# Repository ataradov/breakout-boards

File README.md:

## Breakout Boards

This is a collection of random breakout boards I developed to get started with a new device.

Firmware for the SAM D11 used as a debugger/VCP interface on some boards is available [here](https://github.com/ataradov/free-dap))

### Currrently available boards:

* Atmel SAME70 / SAMS70
* ST STM32G071
* GigaDevice GD32F407V (will probably work for STM32F407 as well)
* Lattice LCMXO256C
* Lattice LCMXO2-2000HC
* Nuvoton M484SIDAE
* Atmel SAMD11 USB Test Board
* Atmel SAMD11 Nano - full breakout with USB connector
* Raspberry Pi RP2040
* Gowin GW1N-UV9QN48

### Errata

The boards are added here at the same time they are submitted for fabrication. There may be issues with them,
but I will not know about them until the boards arrive. Those issues will not be fixed in the files, unless
the boards are really broken and I need to reorder them, or I want to reorder them for some other reason.

Below is a list of known issues:
1. GD32F407V - BOOT0 (pin 94) should be pulled down by a 10 kOhm resistor. This is an easy fix, there is a groud pour near the jumper.
2. SAMD11 USB Test Board - Switch footprint is slightly off (mounting pads are wider than on a real switch).

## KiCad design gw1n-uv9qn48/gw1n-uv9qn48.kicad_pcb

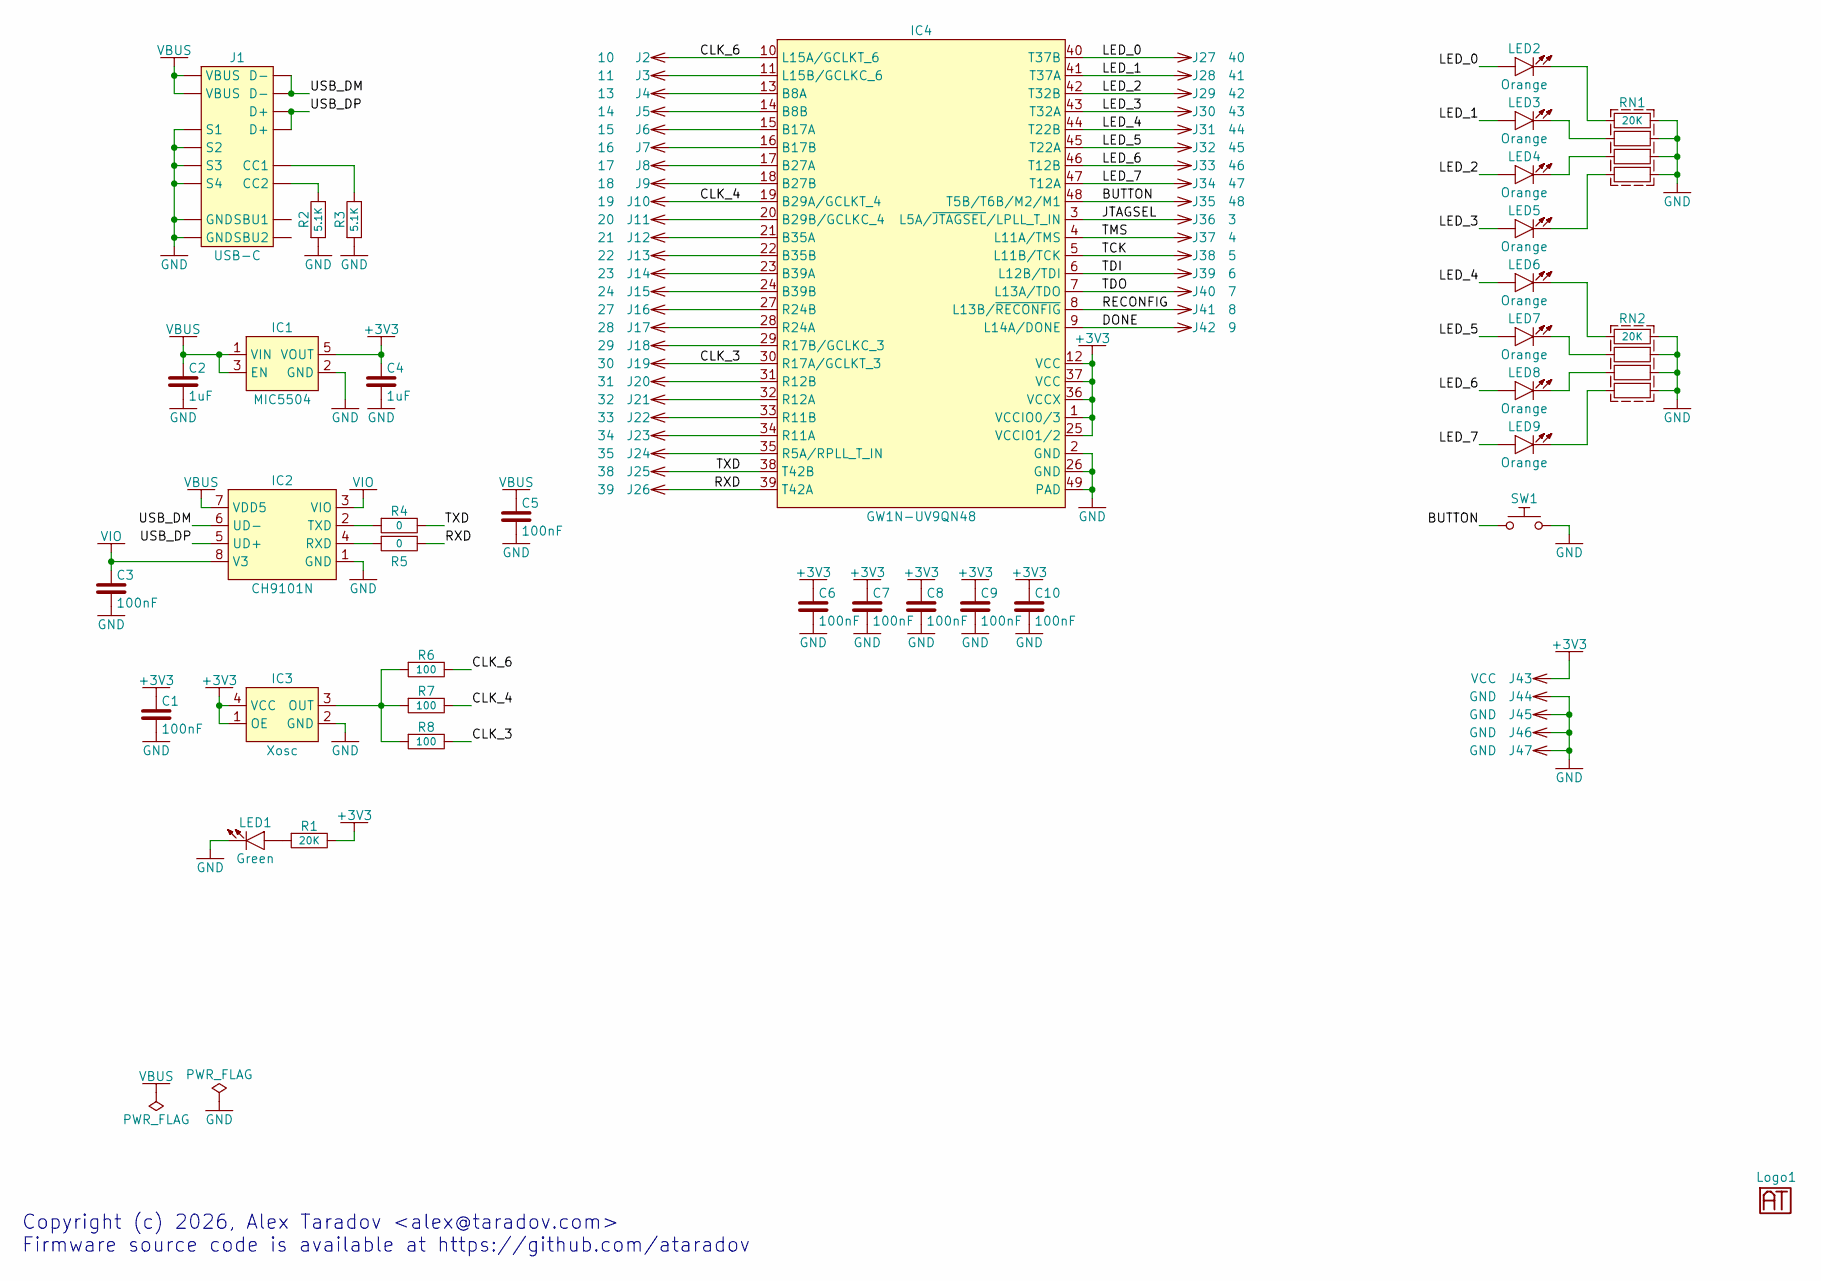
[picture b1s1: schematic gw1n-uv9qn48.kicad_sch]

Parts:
C1, C3, C5, C6, C7, C8, C9, C10: 100nF; 0603
C2, C4: 1uF; 0603
IC1: MIC5504; SOT-23-5
IC2: CH9101N; SO-8
IC3: Xosc; CDFN-4-3.2x2.5mm
IC4: GW1N-UV9QN48; QFN-48-0.4mm
J1: USB-C
J2: 10; Pin-2.54mm
J3: 11; Pin-2.54mm
J4: 13; Pin-2.54mm
J5: 14; Pin-2.54mm
J6: 15; Pin-2.54mm
J7: 16; Pin-2.54mm
J8: 17; Pin-2.54mm
J9: 18; Pin-2.54mm
J10: 19; Pin-2.54mm
J11: 20; Pin-2.54mm
J12: 21; Pin-2.54mm
J13: 22; Pin-2.54mm
J14: 23; Pin-2.54mm
J15: 24; Pin-2.54mm
J16: 27; Pin-2.54mm
J17: 28; Pin-2.54mm
J18: 29; Pin-2.54mm
J19: 30; Pin-2.54mm
J20: 31; Pin-2.54mm
J21: 32; Pin-2.54mm
J22: 33; Pin-2.54mm
J23: 34; Pin-2.54mm
J24: 35; Pin-2.54mm
J25: 38; Pin-2.54mm
J26: 39; Pin-2.54mm
J27: 40; Pin-2.54mm
J28: 41; Pin-2.54mm
J29: 42; Pin-2.54mm
J30: 43; Pin-2.54mm
J31: 44; Pin-2.54mm
J32: 45; Pin-2.54mm
J33: 46; Pin-2.54mm
J34: 47; Pin-2.54mm
J35: 48; Pin-2.54mm
J36: 3; Pin-2.54mm
J37: 4; Pin-2.54mm
J38: 5; Pin-2.54mm
J39: 6; Pin-2.54mm
J40: 7; Pin-2.54mm
J41: 8; Pin-2.54mm
J42: 9; Pin-2.54mm
J43: VCC; Pin-2.54mm
J44, J45, J46, J47: GND; Pin-2.54mm
LED1: Green; 0603_LED
LED2, LED3, LED4, LED5, LED6, LED7, LED8, LED9: Orange; 0603_LED
Logo1: Logo; Logo-Small
R1: 20K; 0603
R2, R3: 5.1K; 0603
R4, R5: 0; 0603
R6, R7, R8: 100; 0603
RN1, RN2: 20K; 0603x4
SW1: TactSwitch; TactSwitch-6mm-Sqare-SMD

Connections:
+3V3: C1.2, C4.2, C6.2, C7.2, C8.2, C9.2, C10.2, IC1.5 (VOUT), IC3.1 (OE), IC3.4 (VCC), IC4.1 (VCCIO0/3), IC4.12 (VCC), IC4.25 (VCCIO1/2), IC4.36 (VCCX), IC4.37 (VCC), J43.1 (1_1), R1.2
/BUTTON: IC4.48 (T5B/T6B/M2/M1), J35.1 (1_1), SW1.1
/CLK_3: IC4.30 (R17A/GCLKT_3), J19.1 (1_1), R8.2
/CLK_4: IC4.19 (B29A/GCLKT_4), J10.1 (1_1), R7.2
/CLK_6: IC4.10 (L15A/GCLKT_6), J2.1 (1_1), R6.2
/DONE: IC4.9 (L14A/DONE), J42.1 (1_1)
/JTAGSEL: IC4.3 (L5A/~JTAGSEL/LPLL_T_IN), J36.1 (1_1)
/LED_0: IC4.40 (T37B), J27.1 (1_1), LED2.1 (A)
/LED_1: IC4.41 (T37A), J28.1 (1_1), LED3.1 (A)
/LED_2: IC4.42 (T32B), J29.1 (1_1), LED4.1 (A)
/LED_3: IC4.43 (T32A), J30.1 (1_1), LED5.1 (A)
/LED_4: IC4.44 (T22B), J31.1 (1_1), LED6.1 (A)
/LED_5: IC4.45 (T22A), J32.1 (1_1), LED7.1 (A)
/LED_6: IC4.46 (T12B), J33.1 (1_1), LED8.1 (A)
/LED_7: IC4.47 (T12A), J34.1 (1_1), LED9.1 (A)
/RECONFIG: IC4.8 (L13B/~RECONFIG), J41.1 (1_1)
/RXD: IC4.39 (T42A), J26.1 (1_1), R5.2
/TCK: IC4.5 (L11B/TCK), J38.1 (1_1)
/TDI: IC4.6 (L12B/TDI), J39.1 (1_1)
/TDO: IC4.7 (L13A/TDO), J40.1 (1_1)
/TMS: IC4.4 (L11A/TMS), J37.1 (1_1)
/TXD: IC4.38 (T42B), J25.1 (1_1), R4.2
/USB_DM: IC2.6 (UD-), J1.D-1 (D-), J1.D-2 (D-)
/USB_DP: IC2.5 (UD+), J1.D+1 (D+), J1.D+2 (D+)
GND: C1.1, C2.1, C3.1, C4.1, C5.1, C6.1, C7.1, C8.1, C9.1, C10.1, IC1.2 (GND), IC2.1 (GND), IC3.2 (GND), IC4.2 (GND), IC4.26 (GND), IC4.49 (PAD), J1.GND1 (GND), J1.GND2 (GND), J1.S1, J1.S2, J1.S3, J1.S4, J44.1 (1_1), J45.1 (1_1), J46.1 (1_1), J47.1 (1_1), LED1.2 (K), R2.1, R3.1, RN1.1, RN1.2, RN1.3, RN1.4, RN2.1, RN2.2, RN2.3, RN2.4, SW1.2
unnamed: IC2.4 (RXD), R5.1
unnamed: IC2.2 (TXD), R4.1
unnamed: IC3.3 (OUT), R6.1, R7.1, R8.1
unnamed: IC4.13 (B8A), J4.1 (1_1)
unnamed: IC4.14 (B8B), J5.1 (1_1)
unnamed: IC4.15 (B17A), J6.1 (1_1)
unnamed: IC4.16 (B17B), J7.1 (1_1)
unnamed: IC4.17 (B27A), J8.1 (1_1)
unnamed: IC4.18 (B27B), J9.1 (1_1)
unnamed: IC4.20 (B29B/GCLKC_4), J11.1 (1_1)
unnamed: IC4.21 (B35A), J12.1 (1_1)
unnamed: IC4.22 (B35B), J13.1 (1_1)
unnamed: IC4.23 (B39A), J14.1 (1_1)
unnamed: IC4.24 (B39B), J15.1 (1_1)
unnamed: IC4.11 (L15B/GCLKC_6), J3.1 (1_1)
unnamed: IC4.35 (R5A/RPLL_T_IN), J24.1 (1_1)
unnamed: IC4.34 (R11A), J23.1 (1_1)
unnamed: IC4.33 (R11B), J22.1 (1_1)
unnamed: IC4.32 (R12A), J21.1 (1_1)
unnamed: IC4.31 (R12B), J20.1 (1_1)
unnamed: IC4.29 (R17B/GCLKC_3), J18.1 (1_1)
unnamed: IC4.28 (R24A), J17.1 (1_1)
unnamed: IC4.27 (R24B), J16.1 (1_1)
unnamed: J1.CC1, R3.2
unnamed: J1.CC2, R2.2
unnamed: LED1.1 (A), R1.1
unnamed: LED2.2 (K), RN1.8
unnamed: LED3.2 (K), RN1.7
unnamed: LED4.2 (K), RN1.6
unnamed: LED5.2 (K), RN1.5
unnamed: LED6.2 (K), RN2.8
unnamed: LED7.2 (K), RN2.7
unnamed: LED8.2 (K), RN2.6
unnamed: LED9.2 (K), RN2.5
VBUS: C2.2, C5.2, IC1.1 (VIN), IC1.3 (EN), IC2.7 (VDD5), J1.VBUS1 (VBUS), J1.VBUS2 (VBUS)
VIO: C3.2, IC2.3 (VIO), IC2.8 (V3)

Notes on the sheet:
Copyright (c) 2026, Alex Taradov <alex@taradov.com> Firmware source code is available at https://github.com/ataradov

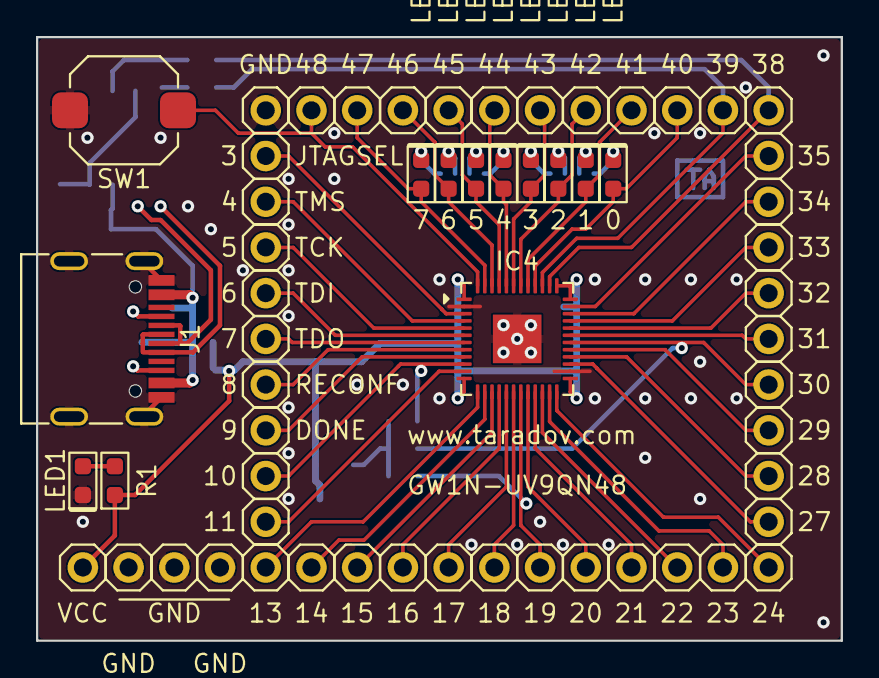
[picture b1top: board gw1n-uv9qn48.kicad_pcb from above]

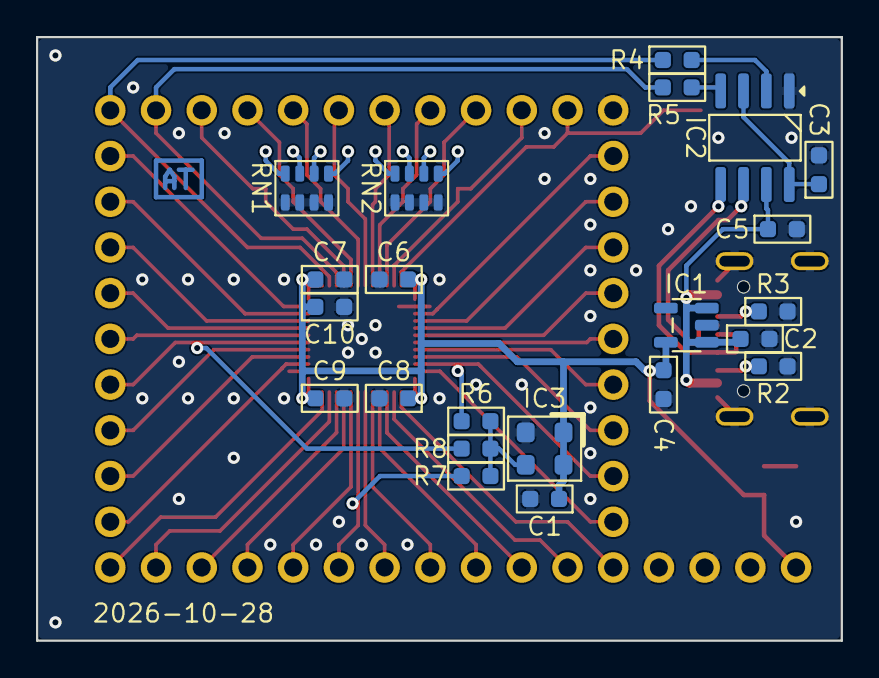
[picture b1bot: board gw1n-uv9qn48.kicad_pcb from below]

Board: 2 copper layers, 44.7 x 33.5 mm, 82 parts (23 on the bottom side), 61 nets.

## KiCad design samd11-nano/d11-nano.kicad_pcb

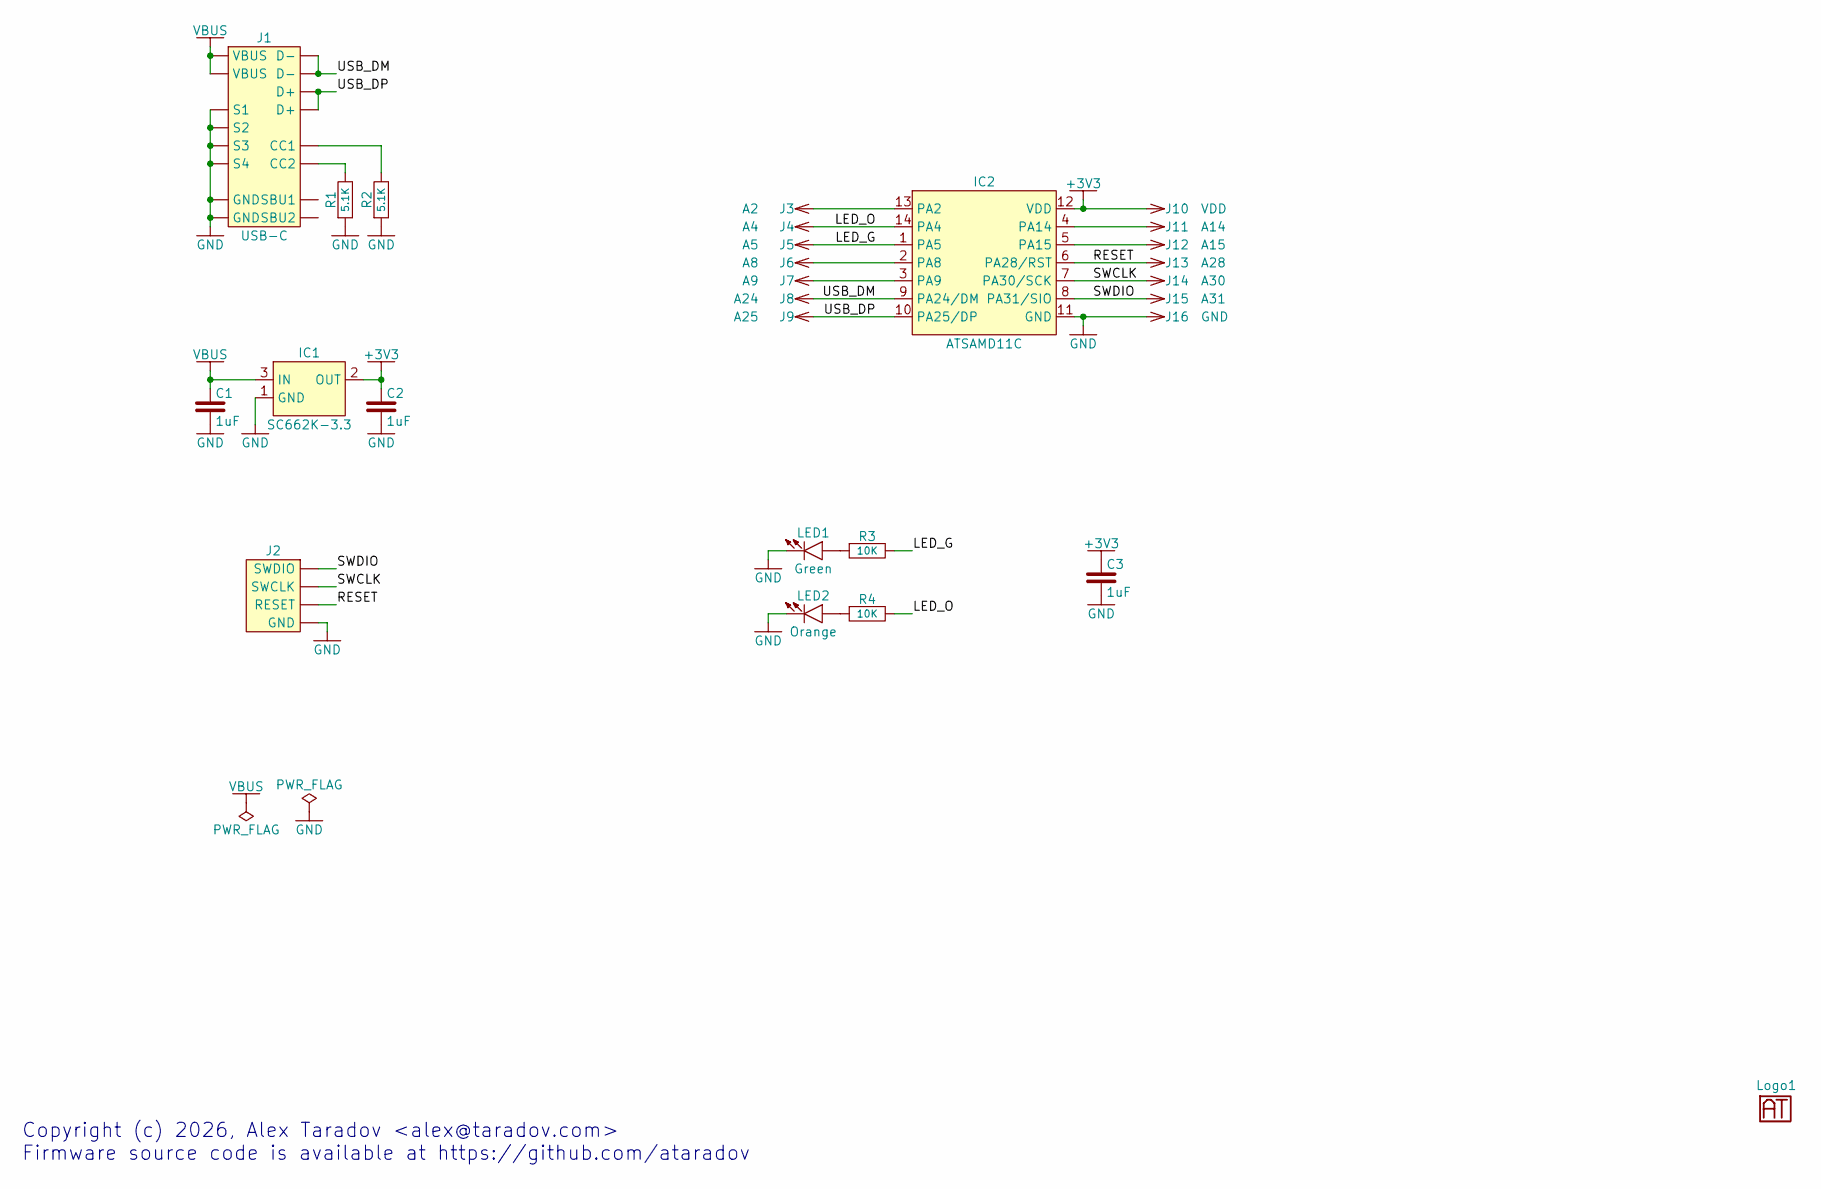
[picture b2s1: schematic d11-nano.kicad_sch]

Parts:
C1, C2, C3: 1uF; 0603
IC1: SC662K-3.3; SOT-23
IC2: ATSAMD11C; SOIC-14
J1: USB-C
J2: Debug; Debug-GDCR-2.54mm-SMD
J3: A2; Pin-2.54mm
J4: A4; Pin-2.54mm
J5: A5; Pin-2.54mm
J6: A8; Pin-2.54mm
J7: A9; Pin-2.54mm
J8: A24; Pin-2.54mm
J9: A25; Pin-2.54mm
J10: VDD; Pin-2.54mm
J11: A14; Pin-2.54mm
J12: A15; Pin-2.54mm
J13: A28; Pin-2.54mm
J14: A30; Pin-2.54mm
J15: A31; Pin-2.54mm
J16: GND; Pin-2.54mm
LED1: Green; 0603_LED
LED2: Orange; 0603_LED
Logo1: Logo; Logo-Small
R1, R2: 5.1K; 0603
R3, R4: 10K; 0603

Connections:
+3V3: C2.2, C3.2, IC1.2 (OUT), IC2.12 (VDD), J10.1 (1_1)
/LED_G: IC2.1 (PA5), J5.1 (1_1), R3.2
/LED_O: IC2.14 (PA4), J4.1 (1_1), R4.2
/RESET: IC2.6 (PA28/RST), J2.RESET, J13.1 (1_1)
/SWCLK: IC2.7 (PA30/SCK), J2.SWCLK, J14.1 (1_1)
/SWDIO: IC2.8 (PA31/SIO), J2.SWDIO, J15.1 (1_1)
/USB_DM: IC2.9 (PA24/DM), J1.D-1 (D-), J1.D-2 (D-), J8.1 (1_1)
/USB_DP: IC2.10 (PA25/DP), J1.D+1 (D+), J1.D+2 (D+), J9.1 (1_1)
GND: C1.1, C2.1, C3.1, IC1.1 (GND), IC2.11 (GND), J1.GND1 (GND), J1.GND2 (GND), J1.S1, J1.S2, J1.S3, J1.S4, J2.GND, J16.1 (1_1), LED1.2 (K), LED2.2 (K), R1.1, R2.1
unnamed: IC2.13 (PA2), J3.1 (1_1)
unnamed: IC2.2 (PA8), J6.1 (1_1)
unnamed: IC2.3 (PA9), J7.1 (1_1)
unnamed: IC2.4 (PA14), J11.1 (1_1)
unnamed: IC2.5 (PA15), J12.1 (1_1)
unnamed: J1.CC1, R2.2
unnamed: J1.CC2, R1.2
unnamed: LED1.1 (A), R3.1
unnamed: LED2.1 (A), R4.1
VBUS: C1.2, IC1.3 (IN), J1.VBUS1 (VBUS), J1.VBUS2 (VBUS)

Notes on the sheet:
Copyright (c) 2026, Alex Taradov <alex@taradov.com> Firmware source code is available at https://github.com/ataradov

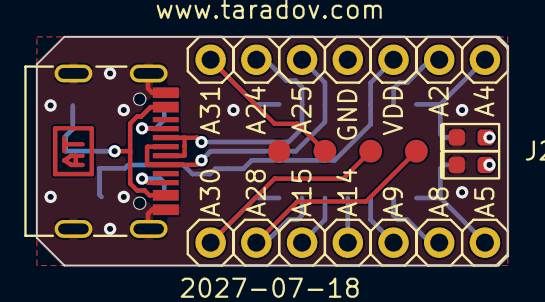
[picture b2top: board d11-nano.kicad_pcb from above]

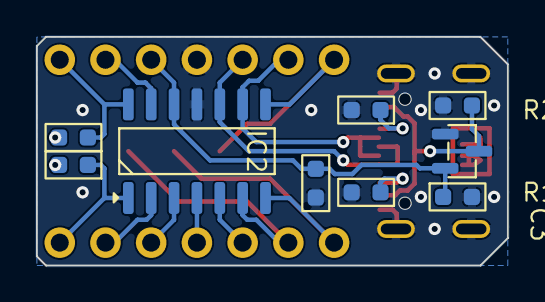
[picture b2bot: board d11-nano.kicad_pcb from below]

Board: 2 copper layers, 26.2 x 12.7 mm, 28 parts (9 on the bottom side), 19 nets.

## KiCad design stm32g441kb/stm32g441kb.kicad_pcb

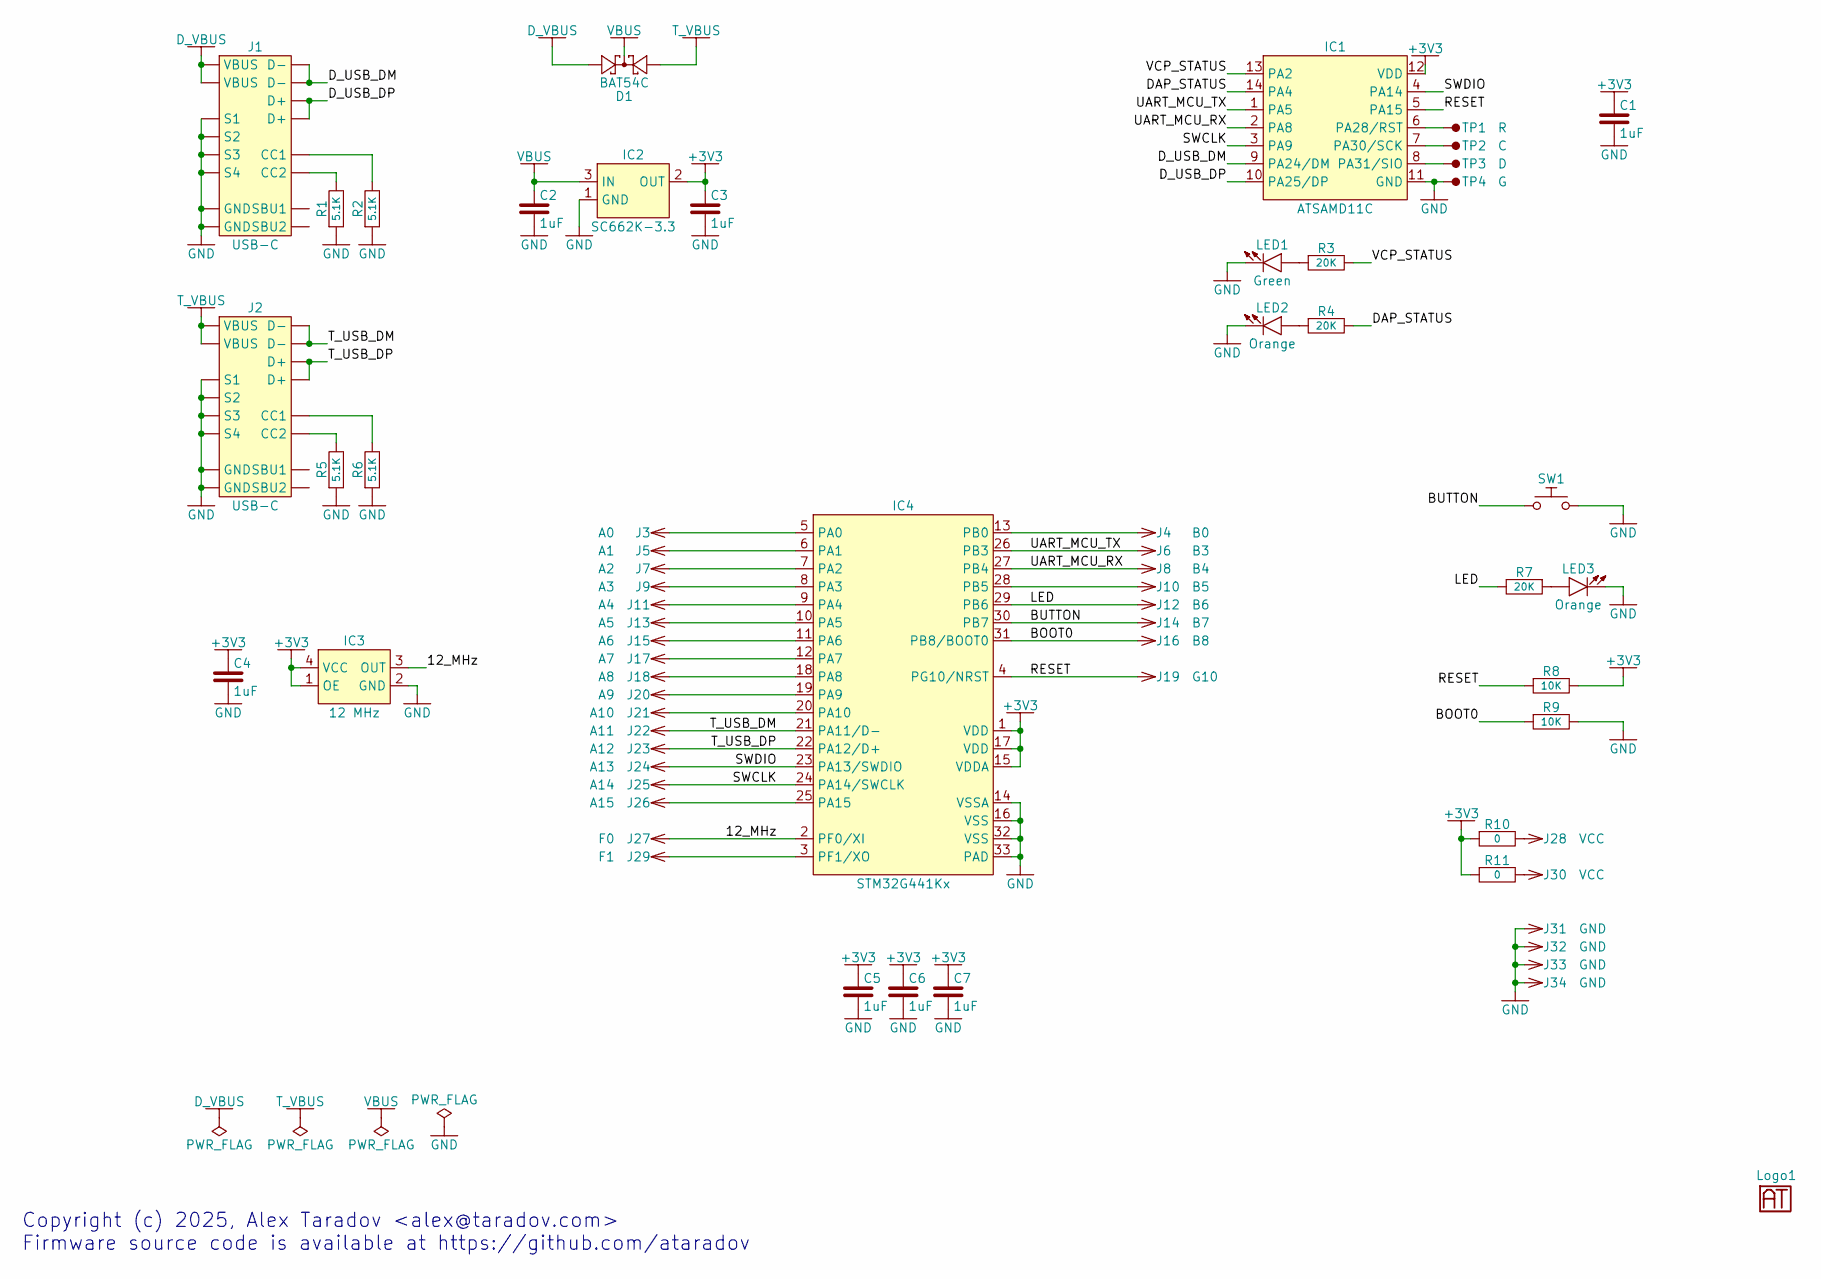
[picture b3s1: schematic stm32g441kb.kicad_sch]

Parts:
C1, C2, C3, C4, C5, C6, C7: 1uF; 0603
D1: BAT54C; SOT-23
IC1: ATSAMD11C; SOIC-14
IC2: SC662K-3.3; SOT-23
IC3: 12 MHz; CDFN-4-3.2x2.5mm
IC4: STM32G441Kx; QFN-32-0.5mm
J1, J2: USB-C
J3: A0; Pin-2.54mm
J4: B0; Pin-2.54mm
J5: A1; Pin-2.54mm
J6: B3; Pin-2.54mm
J7: A2; Pin-2.54mm
J8: B4; Pin-2.54mm
J9: A3; Pin-2.54mm
J10: B5; Pin-2.54mm
J11: A4; Pin-2.54mm
J12: B6; Pin-2.54mm
J13: A5; Pin-2.54mm
J14: B7; Pin-2.54mm
J15: A6; Pin-2.54mm
J16: B8; Pin-2.54mm
J17: A7; Pin-2.54mm
J18: A8; Pin-2.54mm
J19: G10; Pin-2.54mm
J20: A9; Pin-2.54mm
J21: A10; Pin-2.54mm
J22: A11; Pin-2.54mm
J23: A12; Pin-2.54mm
J24: A13; Pin-2.54mm
J25: A14; Pin-2.54mm
J26: A15; Pin-2.54mm
J27: F0; Pin-2.54mm
J28, J30: VCC; Pin-2.54mm
J29: F1; Pin-2.54mm
J31, J32, J33, J34: GND; Pin-2.54mm
LED1: Green; 0603_LED
LED2, LED3: Orange; 0603_LED
Logo1: Logo; Logo-Small
R1, R2, R5, R6: 5.1K; 0603
R3, R4, R7: 20K; 0603
R8, R9: 10K; 0603
R10, R11: 0; 0603
SW1: TactSwitch; TactSwitch-6mm-Sqare-SMD
TP1: R; TestPoint-1.27mm-SMD
TP2: C; TestPoint-1.27mm-SMD
TP3: D; TestPoint-1.27mm-SMD
TP4: G; TestPoint-1.27mm-SMD

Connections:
+3V3: C1.2, C3.2, C4.2, C5.2, C6.2, C7.2, IC1.12 (VDD), IC2.2 (OUT), IC3.1 (OE), IC3.4 (VCC), IC4.1 (VDD), IC4.15 (VDDA), IC4.17 (VDD), R8.2, R10.1, R11.1
/12_MHz: IC3.3 (OUT), IC4.2 (PF0/XI), J27.1
/BOOT0: IC4.31 (PB8/BOOT0), J16.1, R9.1
/BUTTON: IC4.30 (PB7), J14.1, SW1.2
/DAP_STATUS: IC1.14 (PA4), R4.2
/D_USB_DM: IC1.9 (PA24/DM), J1.D-1 (D-), J1.D-2 (D-)
/D_USB_DP: IC1.10 (PA25/DP), J1.D+1 (D+), J1.D+2 (D+)
/LED: IC4.29 (PB6), J12.1, R7.2
/RESET: IC1.5 (PA15), IC4.4 (PG10/NRST), J19.1, R8.1
/SWCLK: IC1.3 (PA9), IC4.24 (PA14/SWCLK), J25.1
/SWDIO: IC1.4 (PA14), IC4.23 (PA13/SWDIO), J24.1
/T_USB_DM: IC4.21 (PA11/D-), J2.D-1 (D-), J2.D-2 (D-), J22.1
/T_USB_DP: IC4.22 (PA12/D+), J2.D+1 (D+), J2.D+2 (D+), J23.1
/UART_MCU_RX: IC1.2 (PA8), IC4.27 (PB4), J8.1
/UART_MCU_TX: IC1.1 (PA5), IC4.26 (PB3), J6.1
/VCP_STATUS: IC1.13 (PA2), R3.2
D_VBUS: D1.2, J1.VBUS1 (VBUS), J1.VBUS2 (VBUS)
GND: C1.1, C2.1, C3.1, C4.1, C5.1, C6.1, C7.1, IC1.11 (GND), IC2.1 (GND), IC3.2 (GND), IC4.14 (VSSA), IC4.16 (VSS), IC4.32 (VSS), IC4.33 (PAD), J1.GND1 (GND), J1.GND2 (GND), J1.S1, J1.S2, J1.S3, J1.S4, J2.GND1 (GND), J2.GND2 (GND), J2.S1, J2.S2, J2.S3, J2.S4, J31.1, J32.1, J33.1, J34.1, LED1.2 (K), LED2.2 (K), LED3.2 (K), R1.1, R2.1, R5.1, R6.1, R9.2, SW1.1, TP4.1
unnamed: IC1.6 (PA28/RST), TP1.1
unnamed: IC1.7 (PA30/SCK), TP2.1
unnamed: IC1.8 (PA31/SIO), TP3.1
unnamed: IC4.5 (PA0), J3.1
unnamed: IC4.6 (PA1), J5.1
unnamed: IC4.7 (PA2), J7.1
unnamed: IC4.8 (PA3), J9.1
unnamed: IC4.9 (PA4), J11.1
unnamed: IC4.10 (PA5), J13.1
unnamed: IC4.11 (PA6), J15.1
unnamed: IC4.12 (PA7), J17.1
unnamed: IC4.18 (PA8), J18.1
unnamed: IC4.19 (PA9), J20.1
unnamed: IC4.20 (PA10), J21.1
unnamed: IC4.25 (PA15), J26.1
unnamed: IC4.13 (PB0), J4.1
unnamed: IC4.28 (PB5), J10.1
unnamed: IC4.3 (PF1/XO), J29.1
unnamed: J1.CC1, R2.2
unnamed: J1.CC2, R1.2
unnamed: J2.CC1, R6.2
unnamed: J2.CC2, R5.2
unnamed: J28.1, R10.2
unnamed: J30.1, R11.2
unnamed: LED1.1 (A), R3.1
unnamed: LED2.1 (A), R4.1
unnamed: LED3.1 (A), R7.1
T_VBUS: D1.1, J2.VBUS1 (VBUS), J2.VBUS2 (VBUS)
VBUS: C2.2, D1.3, IC2.3 (IN)

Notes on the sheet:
Copyright (c) 2025, Alex Taradov <alex@taradov.com> Firmware source code is available at https://github.com/ataradov

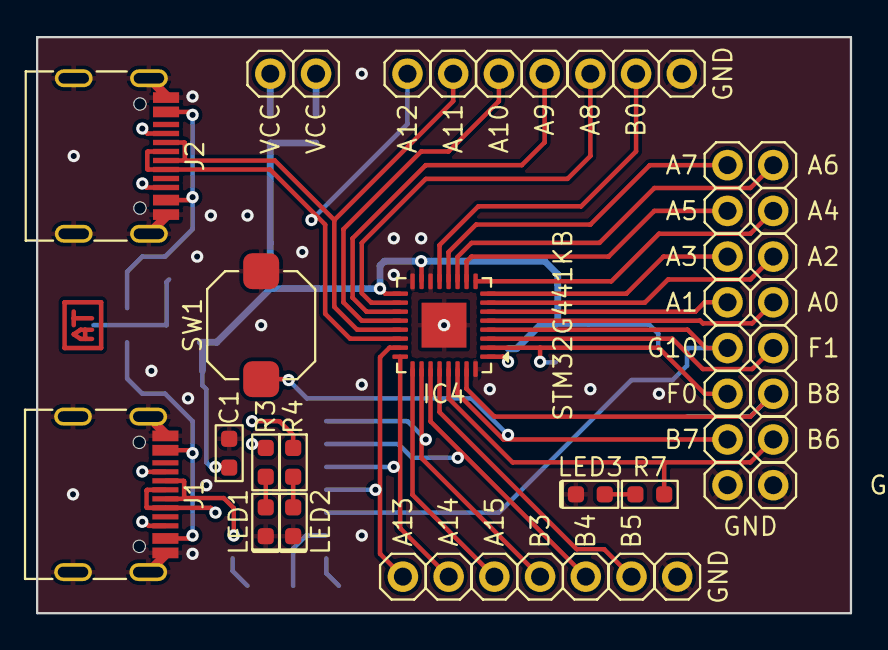
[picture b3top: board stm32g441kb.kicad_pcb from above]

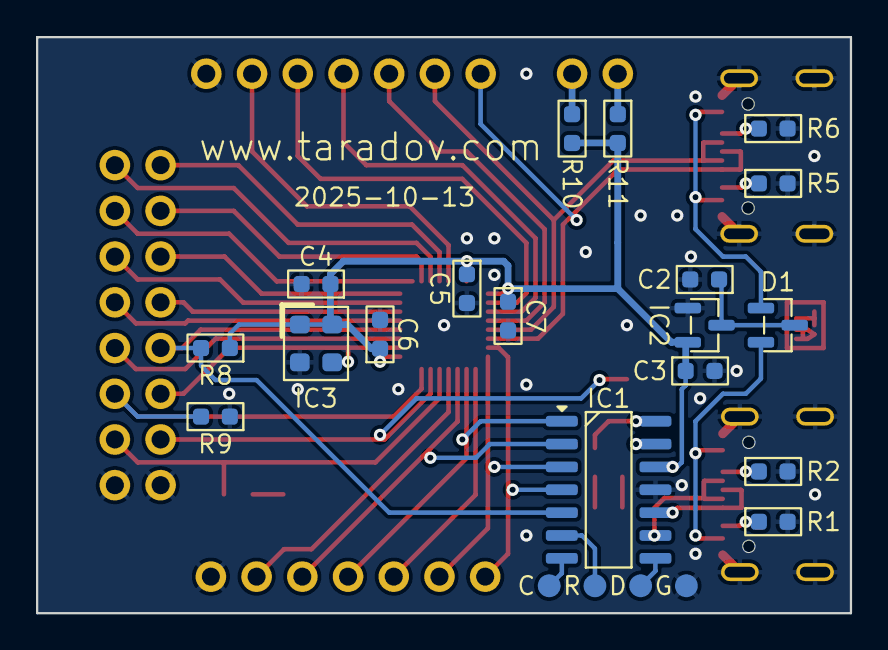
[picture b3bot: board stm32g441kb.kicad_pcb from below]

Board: 2 copper layers, 45.2 x 32.0 mm, 66 parts (22 on the bottom side), 47 nets.

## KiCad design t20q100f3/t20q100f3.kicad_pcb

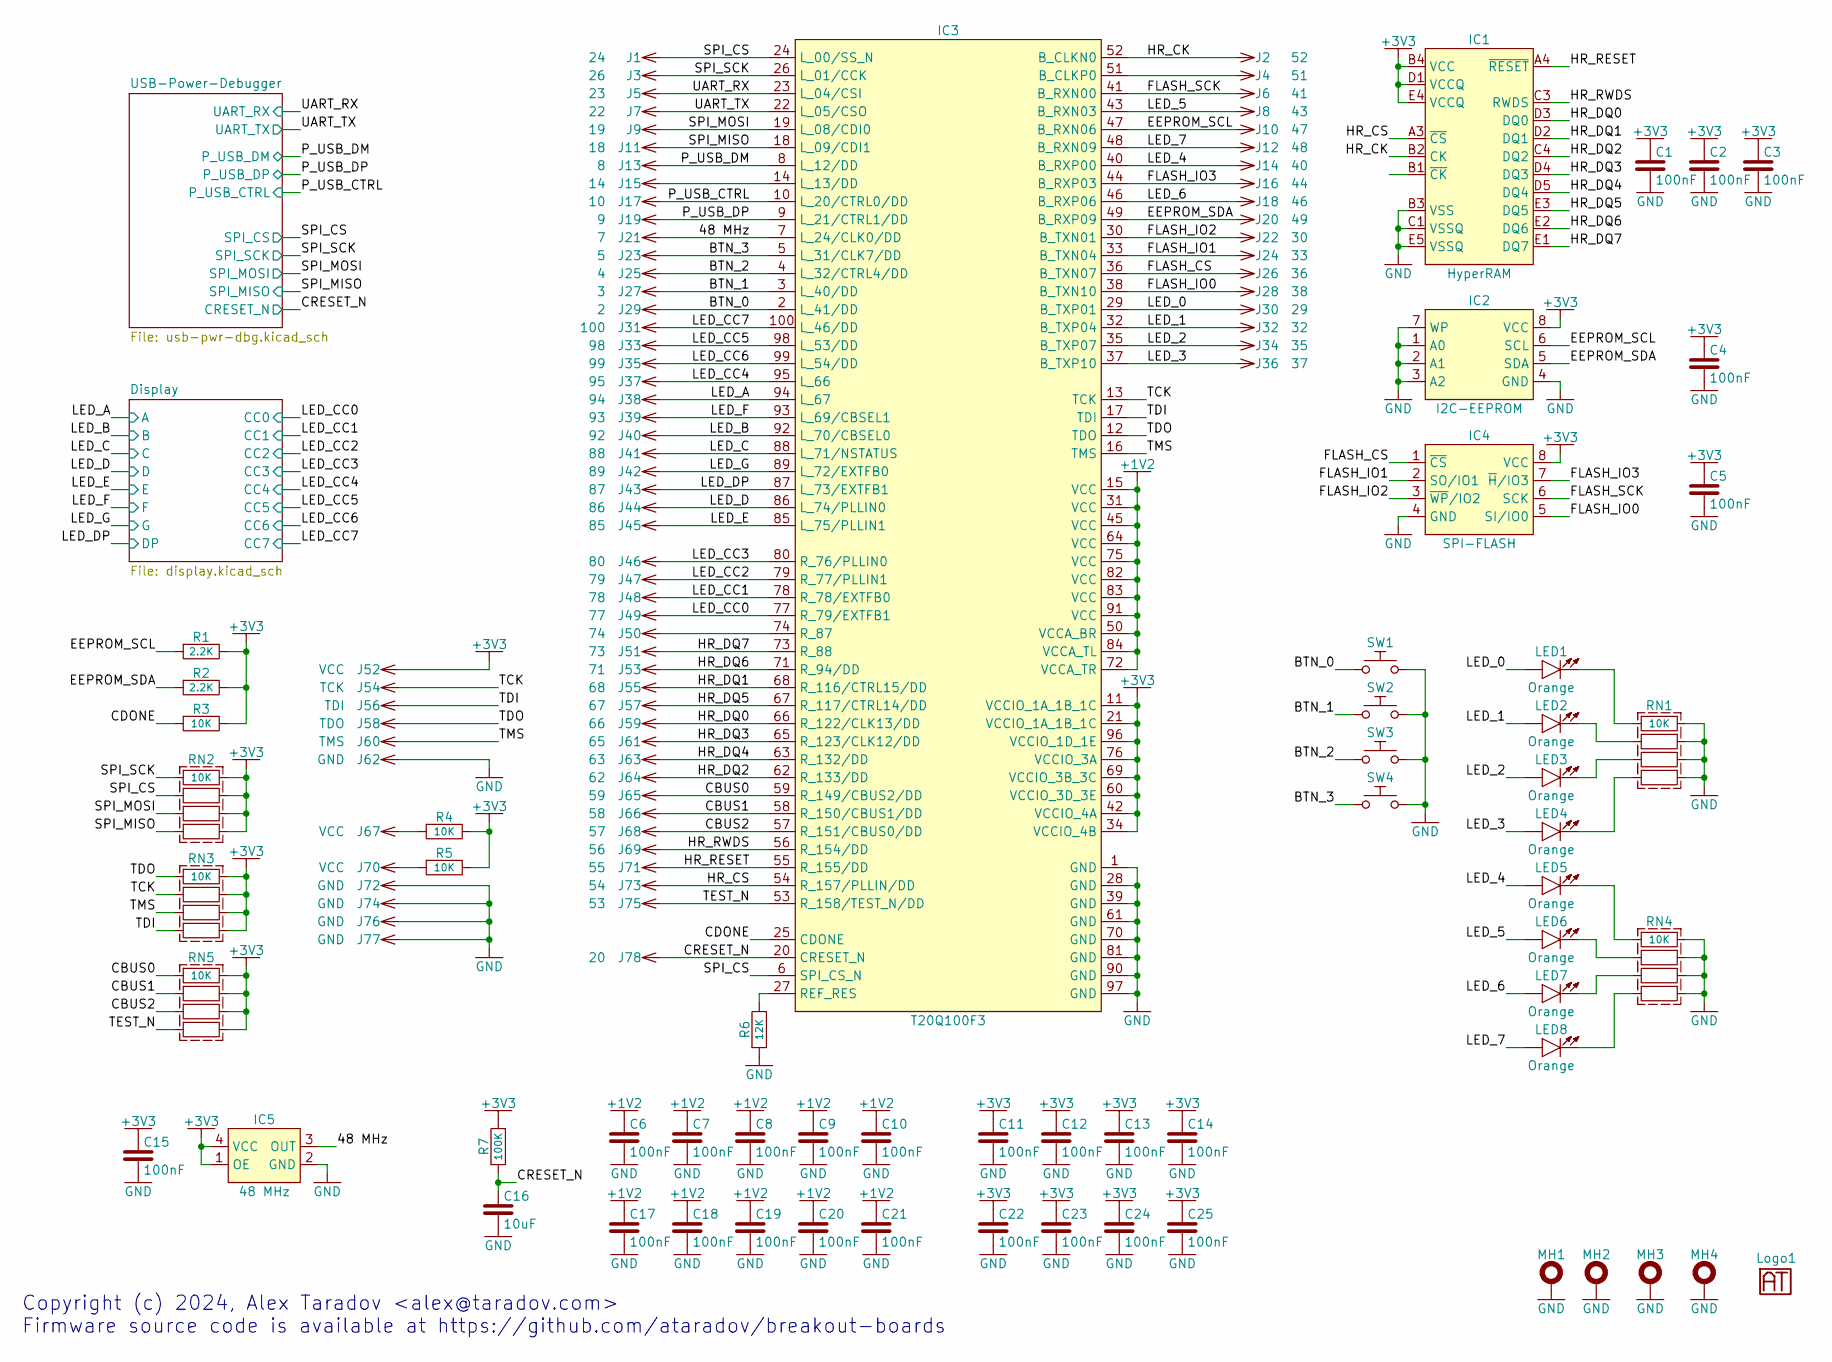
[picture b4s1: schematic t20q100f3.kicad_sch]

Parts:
C1, C2, C3, C4, C5, C6, C7, C8, C9, C10, C11, C12, C13, C14, C15, C17, C18, C19, C20, C21, C22, C23, C24, C25: 100nF; 0603
C16: 10uF; 0603
IC1: HyperRAM; BGA-24-1mm-6x8mm
IC2: I2C-EEPROM; SO-8
IC3: T20Q100F3; TQFP-100-0.5mm
IC4: SPI-FLASH; SO-8
IC5: 48 MHz; CDFN-4-3.2x2.5mm
J1: 24; TestPoint-1.27mm
J2: 52; Pin-2.54mm
J3: 26; TestPoint-1.27mm
J4: 51; Pin-2.54mm
J5: 23; TestPoint-1.27mm
J6: 41; TestPoint-1.27mm
J7: 22; TestPoint-1.27mm
J8: 43; TestPoint-1.27mm
J9: 19; TestPoint-1.27mm
J10: 47; TestPoint-1.27mm
J11: 18; TestPoint-1.27mm
J12: 48; TestPoint-1.27mm
J13: 8; TestPoint-1.27mm
J14: 40; TestPoint-1.27mm
J15: 14; TestPoint-1.27mm
J16: 44; TestPoint-1.27mm
J17: 10; TestPoint-1.27mm
J18: 46; TestPoint-1.27mm
J19: 9; TestPoint-1.27mm
J20: 49; TestPoint-1.27mm
J21: 7; TestPoint-1.27mm
J22: 30; TestPoint-1.27mm
J23: 5; TestPoint-1.27mm
J24: 33; TestPoint-1.27mm
J25: 4; TestPoint-1.27mm
J26: 36; TestPoint-1.27mm
J27: 3; TestPoint-1.27mm
J28: 38; TestPoint-1.27mm
J29: 2; TestPoint-1.27mm
J30: 29; TestPoint-1.27mm
J31: 100; TestPoint-1.27mm
J32: 32; TestPoint-1.27mm
J33: 98; TestPoint-1.27mm
J34: 35; TestPoint-1.27mm
J35: 99; TestPoint-1.27mm
J36: 37; TestPoint-1.27mm
J37: 95; TestPoint-1.27mm
J38: 94; TestPoint-1.27mm
J39: 93; TestPoint-1.27mm
J40: 92; TestPoint-1.27mm
J41: 88; TestPoint-1.27mm
J42: 89; TestPoint-1.27mm
J43: 87; TestPoint-1.27mm
J44: 86; TestPoint-1.27mm
J45: 85; TestPoint-1.27mm
J46: 80; TestPoint-1.27mm
J47: 79; TestPoint-1.27mm
J48: 78; TestPoint-1.27mm
J49: 77; TestPoint-1.27mm
J50: 74; Pin-2.54mm
J51: 73; Pin-2.54mm
J52: VCC; TestPoint-1.27mm
J53: 71; Pin-2.54mm
J54: TCK; TestPoint-1.27mm
J55: 68; Pin-2.54mm
J56: TDI; TestPoint-1.27mm
J57: 67; Pin-2.54mm
J58: TDO; TestPoint-1.27mm
J59: 66; Pin-2.54mm
J60: TMS; TestPoint-1.27mm
J61: 65; Pin-2.54mm
J62: GND; TestPoint-1.27mm
J63: 63; Pin-2.54mm
J64: 62; Pin-2.54mm
J65: 59; Pin-2.54mm
J66: 58; Pin-2.54mm
J67, J70: VCC; Pin-2.54mm
J68: 57; Pin-2.54mm
J69: 56; Pin-2.54mm
J71: 55; Pin-2.54mm
J72, J74, J76, J77: GND; Pin-2.54mm
J73: 54; Pin-2.54mm
J75: 53; Pin-2.54mm
J78: 20; TestPoint-1.27mm
LED1, LED2, LED3, LED4, LED5, LED6, LED7, LED8: Orange; 0603_LED
Logo1: Logo; Logo-Small
MH1, MH2, MH3, MH4: MH-2.5mm-4.0mm
R1, R2: 2.2K; 0603
R3, R4, R5: 10K; 0603
R6: 12K; 0603
R7: 100K; 0603
RN1, RN2, RN3, RN4, RN5: 10K; 0603x4
SW1, SW2, SW3, SW4: TactSwitch; TactSwitch-6mm-Sqare-SMD

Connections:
+1V2: C6.2, C7.2, C8.2, C9.2, C10.2, C17.2, C18.2, C19.2, C20.2, C21.2, IC3.15 (VCC), IC3.31 (VCC), IC3.45 (VCC), IC3.50 (VCCA_BR), IC3.64 (VCC), IC3.72 (VCCA_TR), IC3.75 (VCC), IC3.82 (VCC), IC3.83 (VCC), IC3.84 (VCCA_TL), IC3.91 (VCC); also elsewhere on the board
+3V3: C1.2, C2.2, C3.2, C4.2, C5.2, C11.2, C12.2, C13.2, C14.2, C15.2, C22.2, C23.2, C24.2, C25.2, IC1.B4 (VCC), IC1.D1 (VCCQ), IC1.E4 (VCCQ), IC2.8 (VCC), IC3.11 (VCCIO_1A_1B_1C), IC3.21 (VCCIO_1A_1B_1C), IC3.34 (VCCIO_4B), IC3.42 (VCCIO_4A), IC3.60 (VCCIO_3D_3E), IC3.69 (VCCIO_3B_3C), IC3.76 (VCCIO_3A), IC3.96 (VCCIO_1D_1E), IC4.8 (VCC), IC5.1 (OE), IC5.4 (VCC), J52.1, R1.2, R2.2, R3.2, R4.2, R5.2, R7.2, RN2.5, RN2.6, RN2.7, RN2.8, RN3.5, RN3.6, RN3.7, RN3.8, RN5.5, RN5.6, RN5.7, RN5.8; also elsewhere on the board
/48 MHz: IC3.7 (L_24/CLK0/DD), IC5.3 (OUT), J21.1
/BTN_0: IC3.2 (L_41/DD), J29.1, SW1.1
/BTN_1: IC3.3 (L_40/DD), J27.1, SW2.1
/BTN_2: IC3.4 (L_32/CTRL4/DD), J25.1, SW3.1
/BTN_3: IC3.5 (L_31/CLK7/DD), J23.1, SW4.1
/CBUS0: IC3.59 (R_149/CBUS2/DD), J65.1, RN5.1
/CBUS1: IC3.58 (R_150/CBUS1/DD), J66.1, RN5.2
/CBUS2: IC3.57 (R_151/CBUS0/DD), J68.1, RN5.3
/CDONE: IC3.25 (CDONE), R3.1
/CRESET_N: C16.2, IC3.20 (CRESET_N), J78.1, R7.1; also elsewhere on the board
/EEPROM_SCL: IC2.6 (SCL), IC3.47 (B_RXN06), J10.1, R1.1
/EEPROM_SDA: IC2.5 (SDA), IC3.49 (B_RXP09), J20.1, R2.1
/FLASH_CS: IC3.36 (B_TXN07), IC4.1 (~CS), J26.1
/FLASH_IO0: IC3.38 (B_TXN10), IC4.5 (SI/IO0), J28.1
/FLASH_IO1: IC3.33 (B_TXN04), IC4.2 (SO/IO1), J24.1
/FLASH_IO2: IC3.30 (B_TXN01), IC4.3 (~WP/IO2), J22.1
/FLASH_IO3: IC3.44 (B_RXP03), IC4.7 (~H/IO3), J16.1
/FLASH_SCK: IC3.41 (B_RXN00), IC4.6 (SCK), J6.1
/HR_CK: IC1.B2 (CK), IC3.52 (B_CLKN0), J2.1
/HR_CS: IC1.A3 (~CS), IC3.54 (R_157/PLLIN/DD), J73.1
/HR_DQ0: IC1.D3 (DQ0), IC3.66 (R_122/CLK13/DD), J59.1
/HR_DQ1: IC1.D2 (DQ1), IC3.68 (R_116/CTRL15/DD), J55.1
/HR_DQ2: IC1.C4 (DQ2), IC3.62 (R_133/DD), J64.1
/HR_DQ3: IC1.D4 (DQ3), IC3.65 (R_123/CLK12/DD), J61.1
/HR_DQ4: IC1.D5 (DQ4), IC3.63 (R_132/DD), J63.1
/HR_DQ5: IC1.E3 (DQ5), IC3.67 (R_117/CTRL14/DD), J57.1
/HR_DQ6: IC1.E2 (DQ6), IC3.71 (R_94/DD), J53.1
/HR_DQ7: IC1.E1 (DQ7), IC3.73 (R_88), J51.1
/HR_RESET: IC1.A4 (~RESET), IC3.55 (R_155/DD), J71.1
/HR_RWDS: IC1.C3 (RWDS), IC3.56 (R_154/DD), J69.1
/LED_0: IC3.29 (B_TXP01), J30.1, LED1.1 (A)
/LED_1: IC3.32 (B_TXP04), J32.1, LED2.1 (A)
/LED_2: IC3.35 (B_TXP07), J34.1, LED3.1 (A)
/LED_3: IC3.37 (B_TXP10), J36.1, LED4.1 (A)
/LED_4: IC3.40 (B_RXP00), J14.1, LED5.1 (A)
/LED_5: IC3.43 (B_RXN03), J8.1, LED6.1 (A)
/LED_6: IC3.46 (B_RXP06), J18.1, LED7.1 (A)
/LED_7: IC3.48 (B_RXN09), J12.1, LED8.1 (A)
/LED_A: IC3.94 (L_67), J38.1; also elsewhere on the board
/LED_B: IC3.92 (L_70/CBSEL0), J40.1; also elsewhere on the board
/LED_C: IC3.88 (L_71/NSTATUS), J41.1; also elsewhere on the board
/LED_CC0: IC3.77 (R_79/EXTFB1), J49.1; also elsewhere on the board
/LED_CC1: IC3.78 (R_78/EXTFB0), J48.1; also elsewhere on the board
/LED_CC2: IC3.79 (R_77/PLLIN1), J47.1; also elsewhere on the board
/LED_CC3: IC3.80 (R_76/PLLIN0), J46.1; also elsewhere on the board
/LED_CC4: IC3.95 (L_66), J37.1; also elsewhere on the board
/LED_CC5: IC3.98 (L_53/DD), J33.1; also elsewhere on the board
/LED_CC6: IC3.99 (L_54/DD), J35.1; also elsewhere on the board
/LED_CC7: IC3.100 (L_46/DD), J31.1; also elsewhere on the board
/LED_D: IC3.86 (L_74/PLLIN0), J44.1; also elsewhere on the board
/LED_DP: IC3.87 (L_73/EXTFB1), J43.1; also elsewhere on the board
/LED_E: IC3.85 (L_75/PLLIN1), J45.1; also elsewhere on the board
/LED_F: IC3.93 (L_69/CBSEL1), J39.1; also elsewhere on the board
/LED_G: IC3.89 (L_72/EXTFB0), J42.1; also elsewhere on the board
/P_USB_CTRL: IC3.10 (L_20/CTRL0/DD), J17.1; also elsewhere on the board
/P_USB_DM: IC3.8 (L_12/DD), J13.1; also elsewhere on the board
/P_USB_DP: IC3.9 (L_21/CTRL1/DD), J19.1; also elsewhere on the board
/SPI_CS: IC3.6 (SPI_CS_N), IC3.24 (L_00/SS_N), J1.1, RN2.2; also elsewhere on the board
/SPI_MISO: IC3.18 (L_09/CDI1), J11.1, RN2.4; also elsewhere on the board
/SPI_MOSI: IC3.19 (L_08/CDI0), J9.1, RN2.3; also elsewhere on the board
/SPI_SCK: IC3.26 (L_01/CCK), J3.1, RN2.1; also elsewhere on the board
/TCK: IC3.13 (TCK), J54.1, RN3.2
/TDI: IC3.17 (TDI), J56.1, RN3.4
/TDO: IC3.12 (TDO), J58.1, RN3.1
/TEST_N: IC3.53 (R_158/TEST_N/DD), J75.1, RN5.4
/TMS: IC3.16 (TMS), J60.1, RN3.3
/UART_RX: IC3.23 (L_04/CSI), J5.1; also elsewhere on the board
/UART_TX: IC3.22 (L_05/CSO), J7.1; also elsewhere on the board
GND: C1.1, C2.1, C3.1, C4.1, C5.1, C6.1, C7.1, C8.1, C9.1, C10.1, C11.1, C12.1, C13.1, C14.1, C15.1, C16.1, C17.1, C18.1, C19.1, C20.1, C21.1, C22.1, C23.1, C24.1, C25.1, IC1.B3 (VSS), IC1.C1 (VSSQ), IC1.E5 (VSSQ), IC2.1 (A0), IC2.2 (A1), IC2.3 (A2), IC2.4 (GND), IC2.7 (WP), IC3.1 (GND), IC3.28 (GND), IC3.39 (GND), IC3.61 (GND), IC3.70 (GND), IC3.81 (GND), IC3.90 (GND), IC3.97 (GND), IC4.4 (GND), IC5.2 (GND), J62.1, J72.1, J74.1, J76.1, J77.1, MH1.1, MH2.1, MH3.1, MH4.1, R6.1, RN1.1, RN1.2, RN1.3, RN1.4, RN4.1, RN4.2, RN4.3, RN4.4, SW1.2, SW2.2, SW3.2, SW4.2; also elsewhere on the board
unnamed: IC3.51 (B_CLKP0), J4.1
unnamed: IC3.14 (L_13/DD), J15.1
unnamed: IC3.27 (REF_RES), R6.2
unnamed: IC3.74 (R_87), J50.1
unnamed: J67.1, R4.1
unnamed: J70.1, R5.1
unnamed: LED1.2 (K), RN1.8
unnamed: LED2.2 (K), RN1.7
unnamed: LED3.2 (K), RN1.6
unnamed: LED4.2 (K), RN1.5
unnamed: LED5.2 (K), RN4.8
unnamed: LED6.2 (K), RN4.7
unnamed: LED7.2 (K), RN4.6
unnamed: LED8.2 (K), RN4.5

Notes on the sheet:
Copyright (c) 2024, Alex Taradov <alex@taradov.com> Firmware source code is available at https://github.com/ataradov/breakout-boards
